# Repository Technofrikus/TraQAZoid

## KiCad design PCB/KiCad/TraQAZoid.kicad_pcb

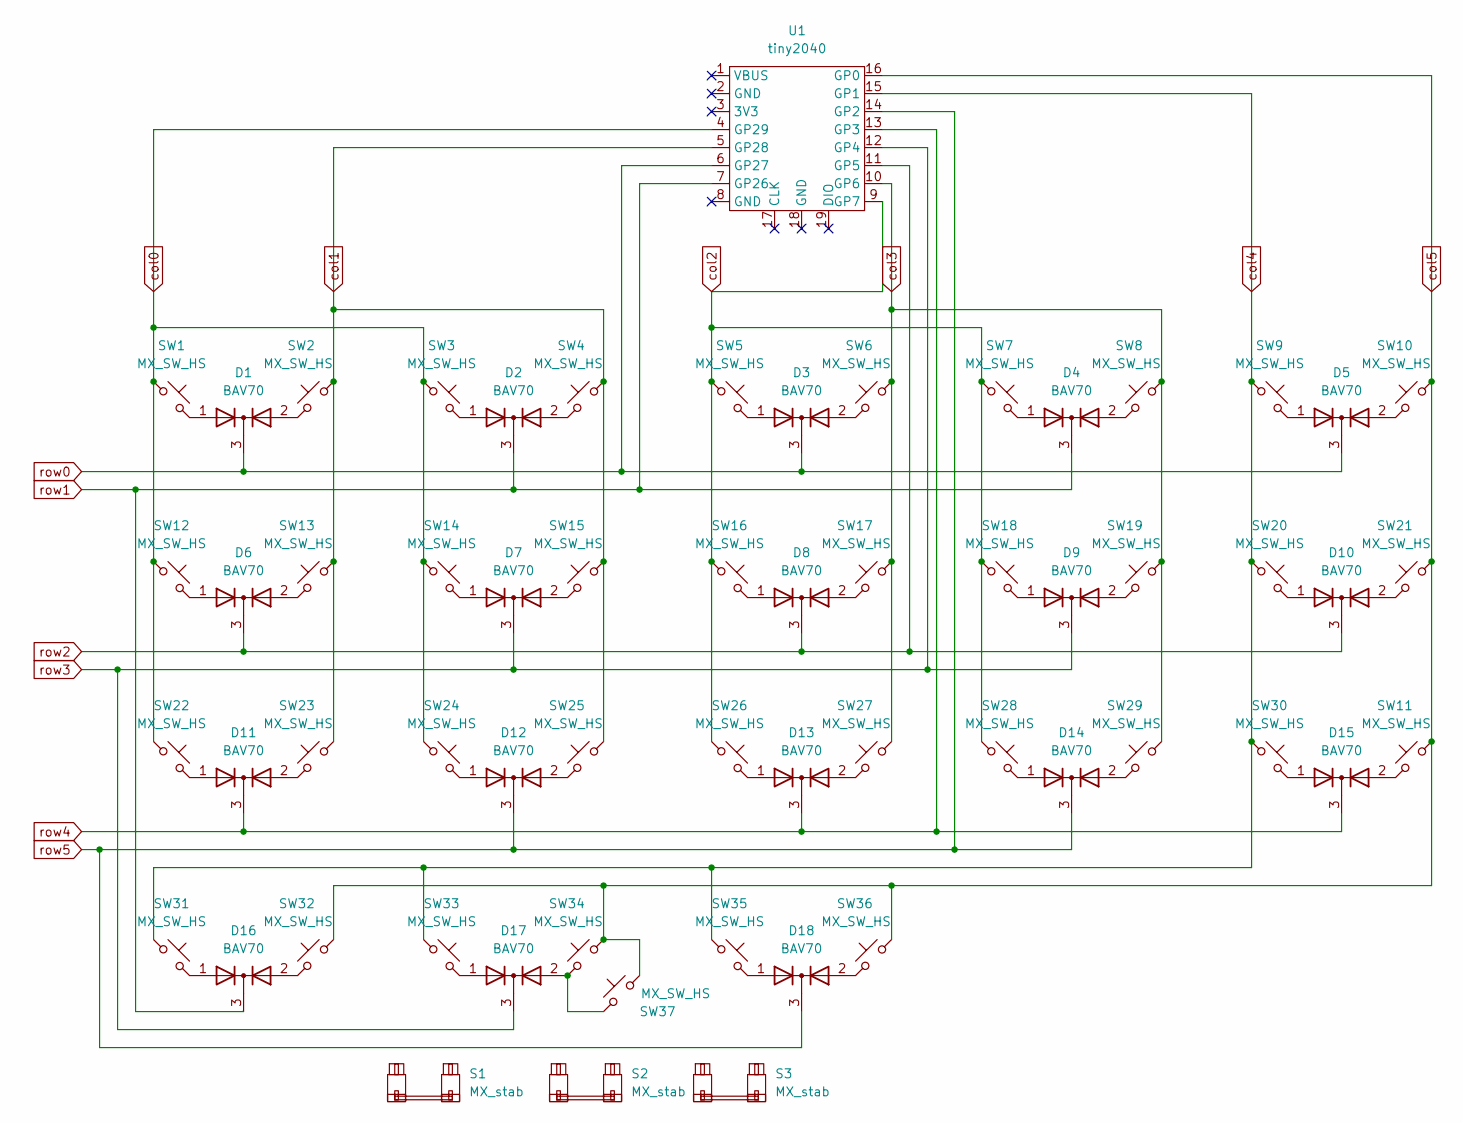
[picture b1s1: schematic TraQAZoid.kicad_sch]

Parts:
D1, D2, D3, D4, D5, D6, D7, D8, D9, D10, D11, D12, D13, D14, D15, D16, D17, D18: BAV70; SOT-23
S1, S3: MX_stab; STAB_MX_P_2u
S2: MX_stab; STAB_MX_P_7u
SW1, SW2, SW3, SW4, SW5, SW6, SW7, SW8, SW9, SW10, SW11, SW12, SW13, SW14, SW15, SW16, SW17, SW18, SW19, SW20, SW21, SW22, SW23, SW24, SW25, SW26, SW27, SW28, SW29, SW30, SW31, SW32, SW33, SW34, SW35, SW36, SW37: MX_SW_HS; SW_Kailh_socket_MX_optional
U1: tiny2040

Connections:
unnamed: D2.1 (A), SW3.2
unnamed: D2.2 (A), SW4.1
unnamed: D3.1 (A), SW5.2
unnamed: D3.2 (A), SW6.1
unnamed: D4.1 (A), SW7.2
unnamed: D4.2 (A), SW8.1
unnamed: D5.1 (A), SW9.2
unnamed: D5.2 (A), SW10.1
unnamed: D6.1 (A), SW12.2
unnamed: D6.2 (A), SW13.1
unnamed: D7.1 (A), SW14.2
unnamed: D7.2 (A), SW15.1
unnamed: D8.1 (A), SW16.2
unnamed: D8.2 (A), SW17.1
unnamed: D9.1 (A), SW18.2
unnamed: D9.2 (A), SW19.1
unnamed: D10.1 (A), SW20.2
unnamed: D10.2 (A), SW21.1
unnamed: D11.1 (A), SW22.2
unnamed: D11.2 (A), SW23.1
unnamed: D12.1 (A), SW24.2
unnamed: D12.2 (A), SW25.1
unnamed: D13.1 (A), SW26.2
unnamed: D13.2 (A), SW27.1
unnamed: D14.1 (A), SW28.2
unnamed: D14.2 (A), SW29.1
unnamed: D1.1 (A), SW1.2
unnamed: D1.2 (A), SW2.1
unnamed: D15.2 (A), SW11.1
unnamed: D15.1 (A), SW30.2
unnamed: D16.1 (A), SW31.2
unnamed: D16.2 (A), SW32.1
unnamed: D17.1 (A), SW33.2
unnamed: D18.1 (A), SW35.2
unnamed: D18.2 (A), SW36.1
unnamed: D17.2 (A), SW34.1, SW37.1
col0: SW1.1, SW3.1, SW12.1, SW14.1, SW22.1, SW24.1, U1.4 (GP29)
col1: SW2.2, SW4.2, SW13.2, SW15.2, SW23.2, SW25.2, U1.5 (GP28)
col2: SW5.1, SW7.1, SW16.1, SW18.1, SW26.1, SW28.1, U1.9 (GP7)
col3: SW6.2, SW8.2, SW17.2, SW19.2, SW27.2, SW29.2, U1.10 (GP6)
col4: SW9.1, SW20.1, SW30.1, SW31.1, SW33.1, SW35.1, U1.15 (GP1)
col5: SW10.2, SW11.2, SW21.2, SW32.2, SW34.2, SW36.2, SW37.2, U1.16 (GP0)
row0: D1.3 (K), D3.3 (K), D5.3 (K), U1.6 (GP27)
row1: D2.3 (K), D4.3 (K), D16.3 (K), U1.7 (GP26)
row2: D6.3 (K), D8.3 (K), D10.3 (K), U1.11 (GP5)
row3: D7.3 (K), D9.3 (K), D17.3 (K), U1.12 (GP4)
row4: D11.3 (K), D13.3 (K), D15.3 (K), U1.13 (GP3)
row5: D12.3 (K), D14.3 (K), D18.3 (K), U1.14 (GP2)

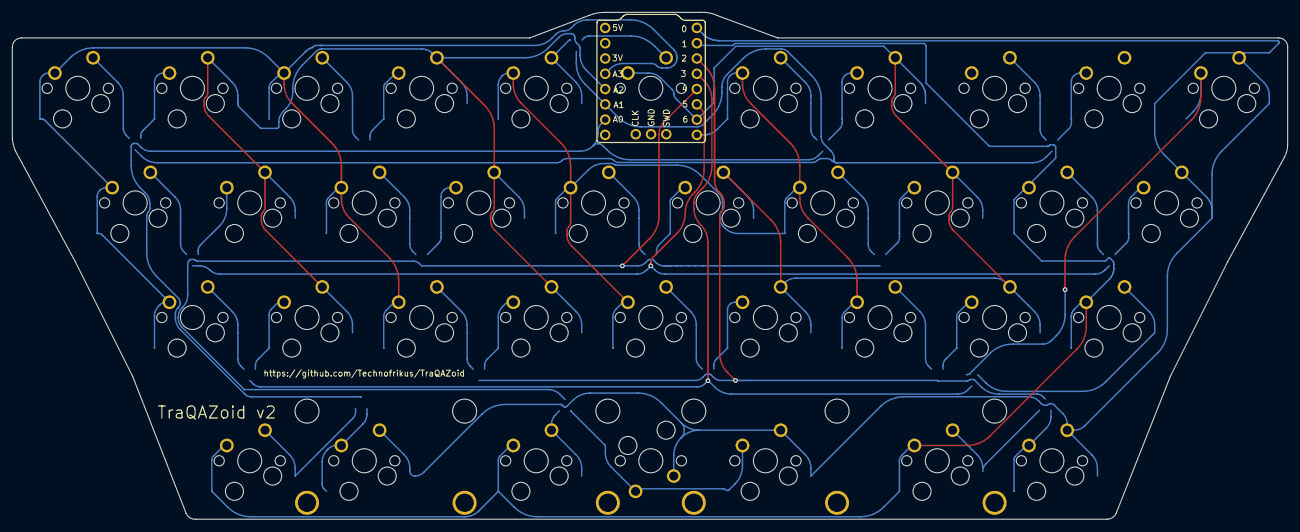
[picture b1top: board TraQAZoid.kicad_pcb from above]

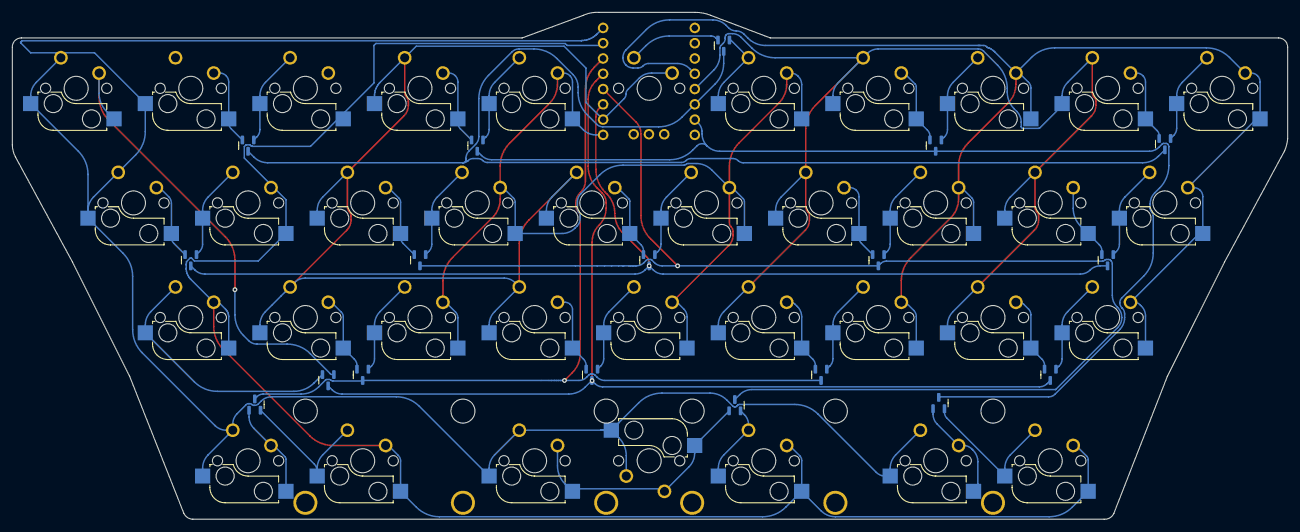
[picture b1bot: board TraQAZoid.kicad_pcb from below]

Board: 2 copper layers, 212.0 x 84.3 mm, 59 parts (18 on the bottom side), 48 nets.

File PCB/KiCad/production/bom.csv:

Designator,Footprint,Quantity,Value,LCSC Part #
"D1, D10, D11, D12, D13, D14, D15, D16, D17, D18, D2, D3, D4, D5, D6, D7, D8, D9",SOT-23,18,BAV70,
"S1, S3",STAB_MX_P_2u,2,MX_stab,
S2,STAB_MX_P_7u,1,MX_stab,
"SW1, SW10, SW11, SW12, SW13, SW14, SW15, SW16, SW17, SW18, SW19, SW2, SW20, SW21, SW22, SW23, SW24, SW25, SW26, SW27, SW28, SW29, SW3, SW30, SW31, SW32, SW33, SW34, SW35, SW36, SW37, SW4, SW5, SW7, SW8, SW9",SW_Kailh_socket_MX_optional,36,MX_SW_HS,
SW6,SW_MX,1,MX_SW_HS,
U1,tiny2040,1,tiny2040,

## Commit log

2022-12-17 Added Submodules
2022-12-17 More Submodules
2022-12-30 Gerber and Screenshots of v1 PCB, because KiCAD files are lost because of an user error
2022-12-30 3D of the PCB v1
2023-01-06 Firmware angefangen
2023-01-06 Schematic fertig, denke ich
2023-01-07 Sicherung
2023-01-07 Fertig?
2023-01-13 Firmware für v2 geschrieben und funktioniert (in VIAL, ohne PCB-Test)
2023-01-14 PCB kleiner gemacht.
